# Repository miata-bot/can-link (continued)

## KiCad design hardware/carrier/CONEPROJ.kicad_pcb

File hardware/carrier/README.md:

# Carrier Board

This is the "top" half of the device. It does power management, CAN communication and output control.

## Major Components

| Name | Description |
| ---- | ----------- |
| RP2040 | Main MCU. dual core ARM M0 |
| 3.3v automotive regulator | Power supply for radio, CAN transciever, CAN interface and RP2040 |
| 5.0V automotive regulator | Power supply for the `platform` board |
| RFM69 Packet radio | Packet radio for wireless syncronization |
| Motor driver | 2 motor output motor driver |
| Dual footprint MCP2515 CAN interface | Very popular CAN interface IC. Both packages are placed in the case that one cannot be obtained |
| CAN transciever | driver for CAN communication |
| 2 Buttons | what can i say about buttons |
| 3 status LEDS | control em however u want |
| WS15 LED | first node in a chain of individually addressable LEDS |

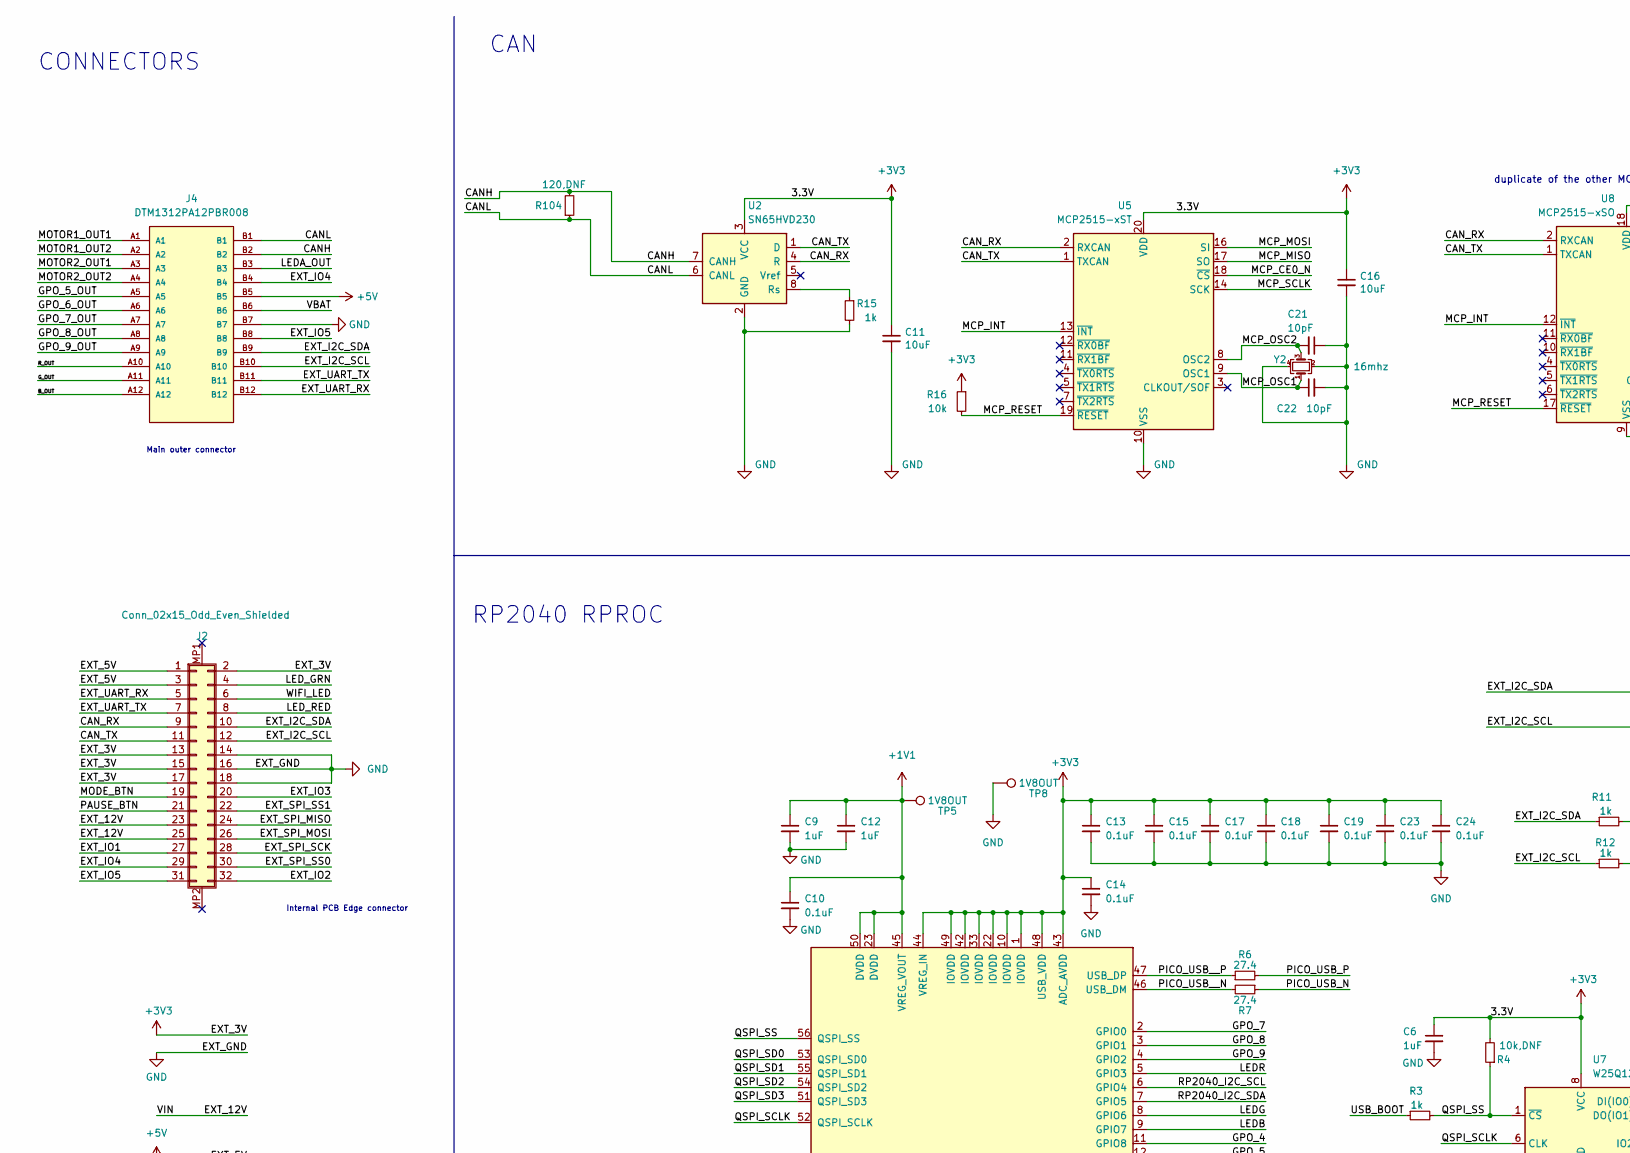
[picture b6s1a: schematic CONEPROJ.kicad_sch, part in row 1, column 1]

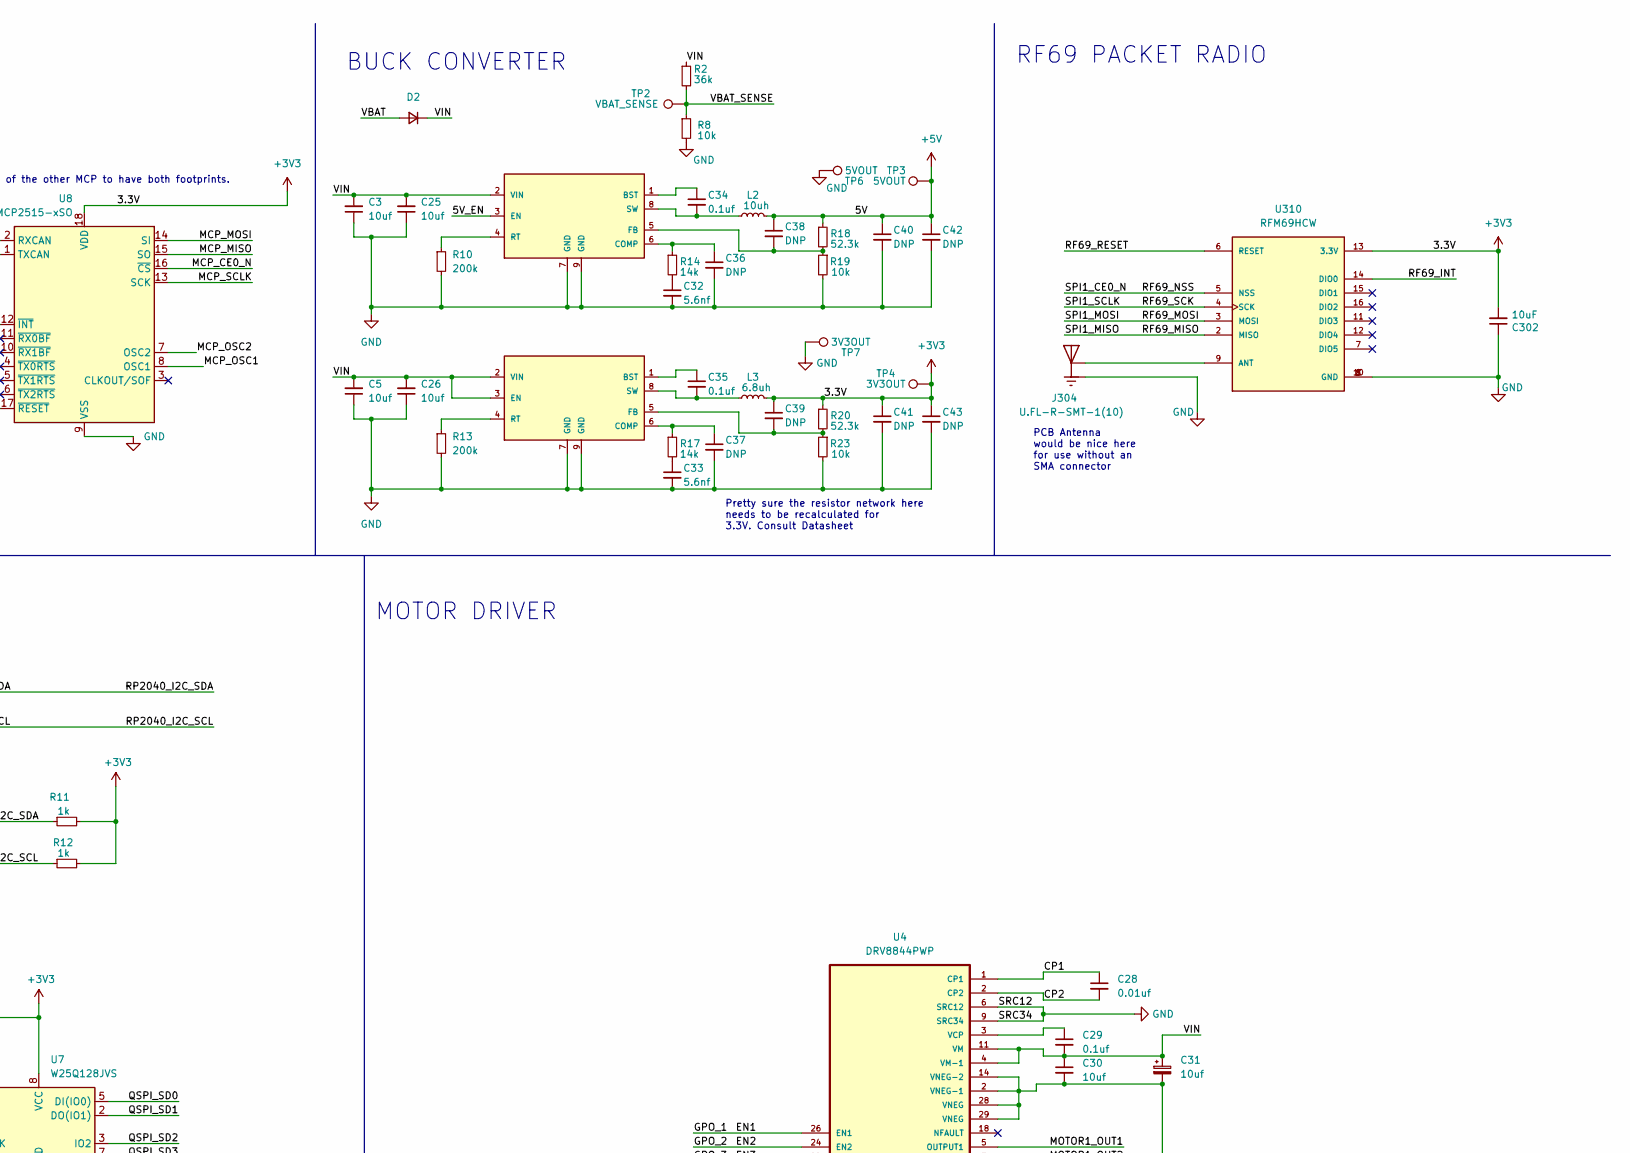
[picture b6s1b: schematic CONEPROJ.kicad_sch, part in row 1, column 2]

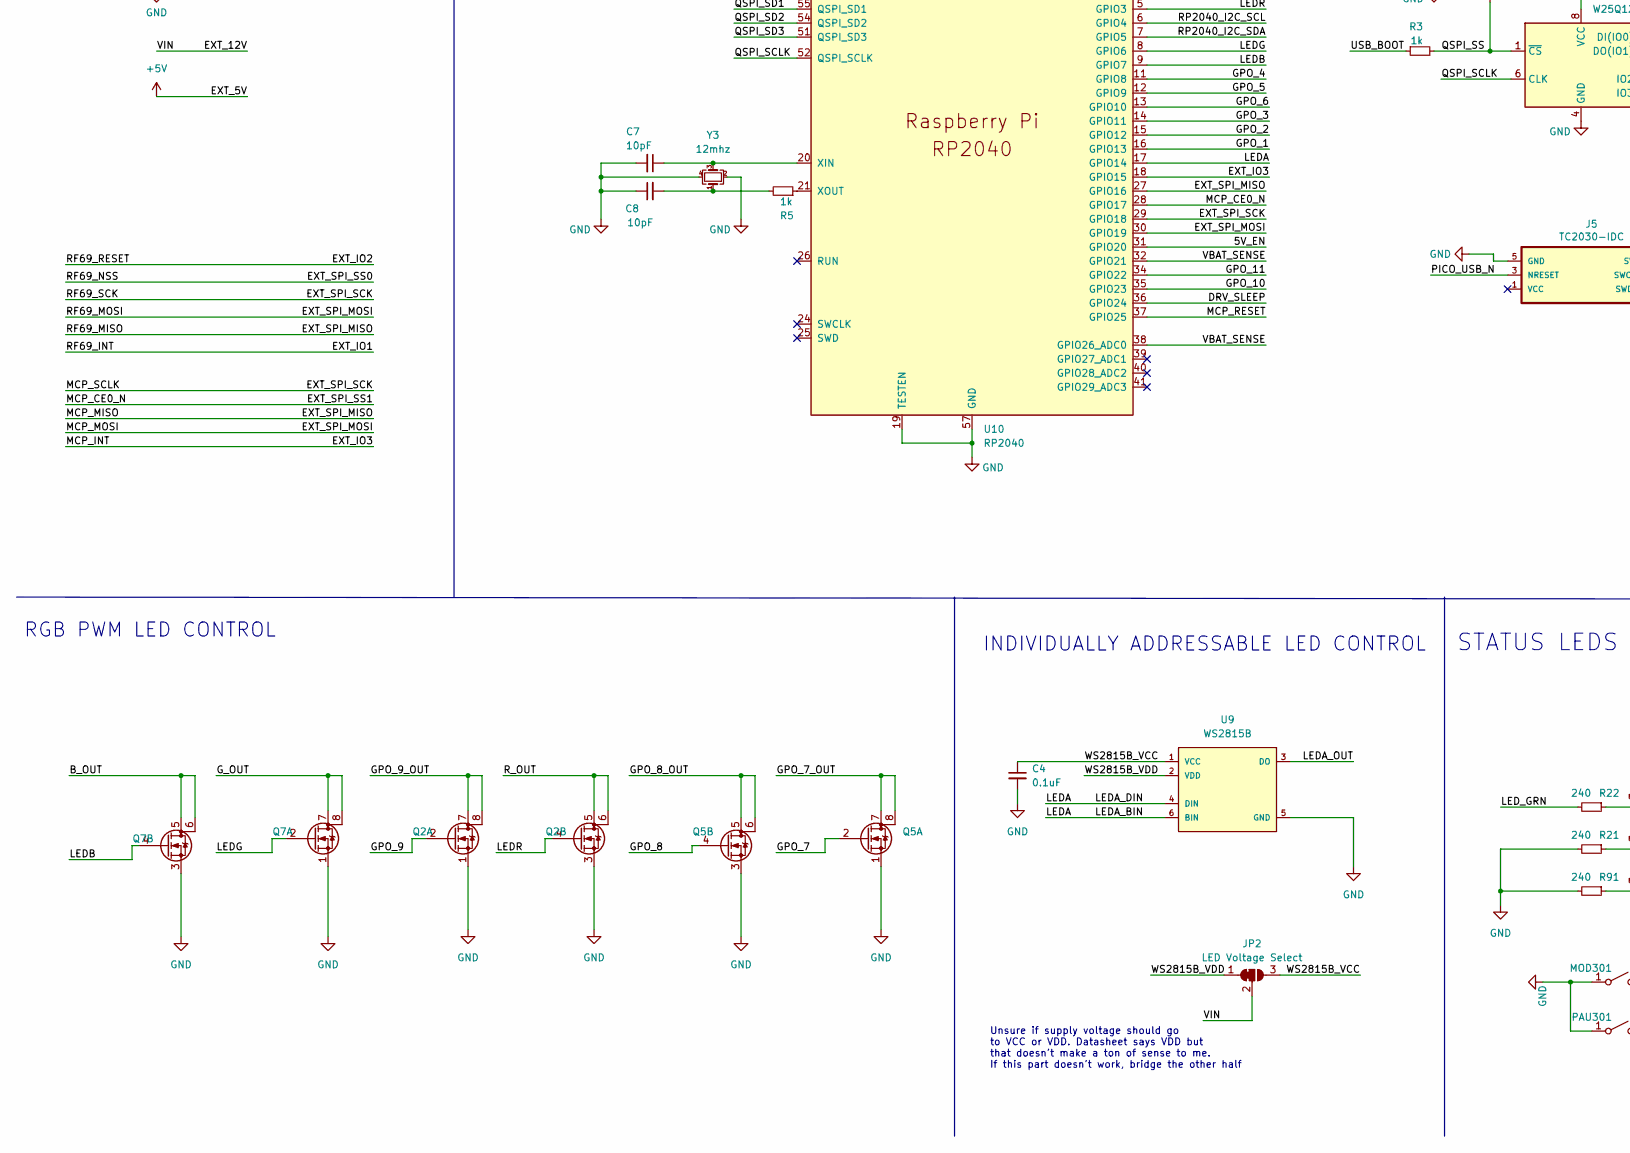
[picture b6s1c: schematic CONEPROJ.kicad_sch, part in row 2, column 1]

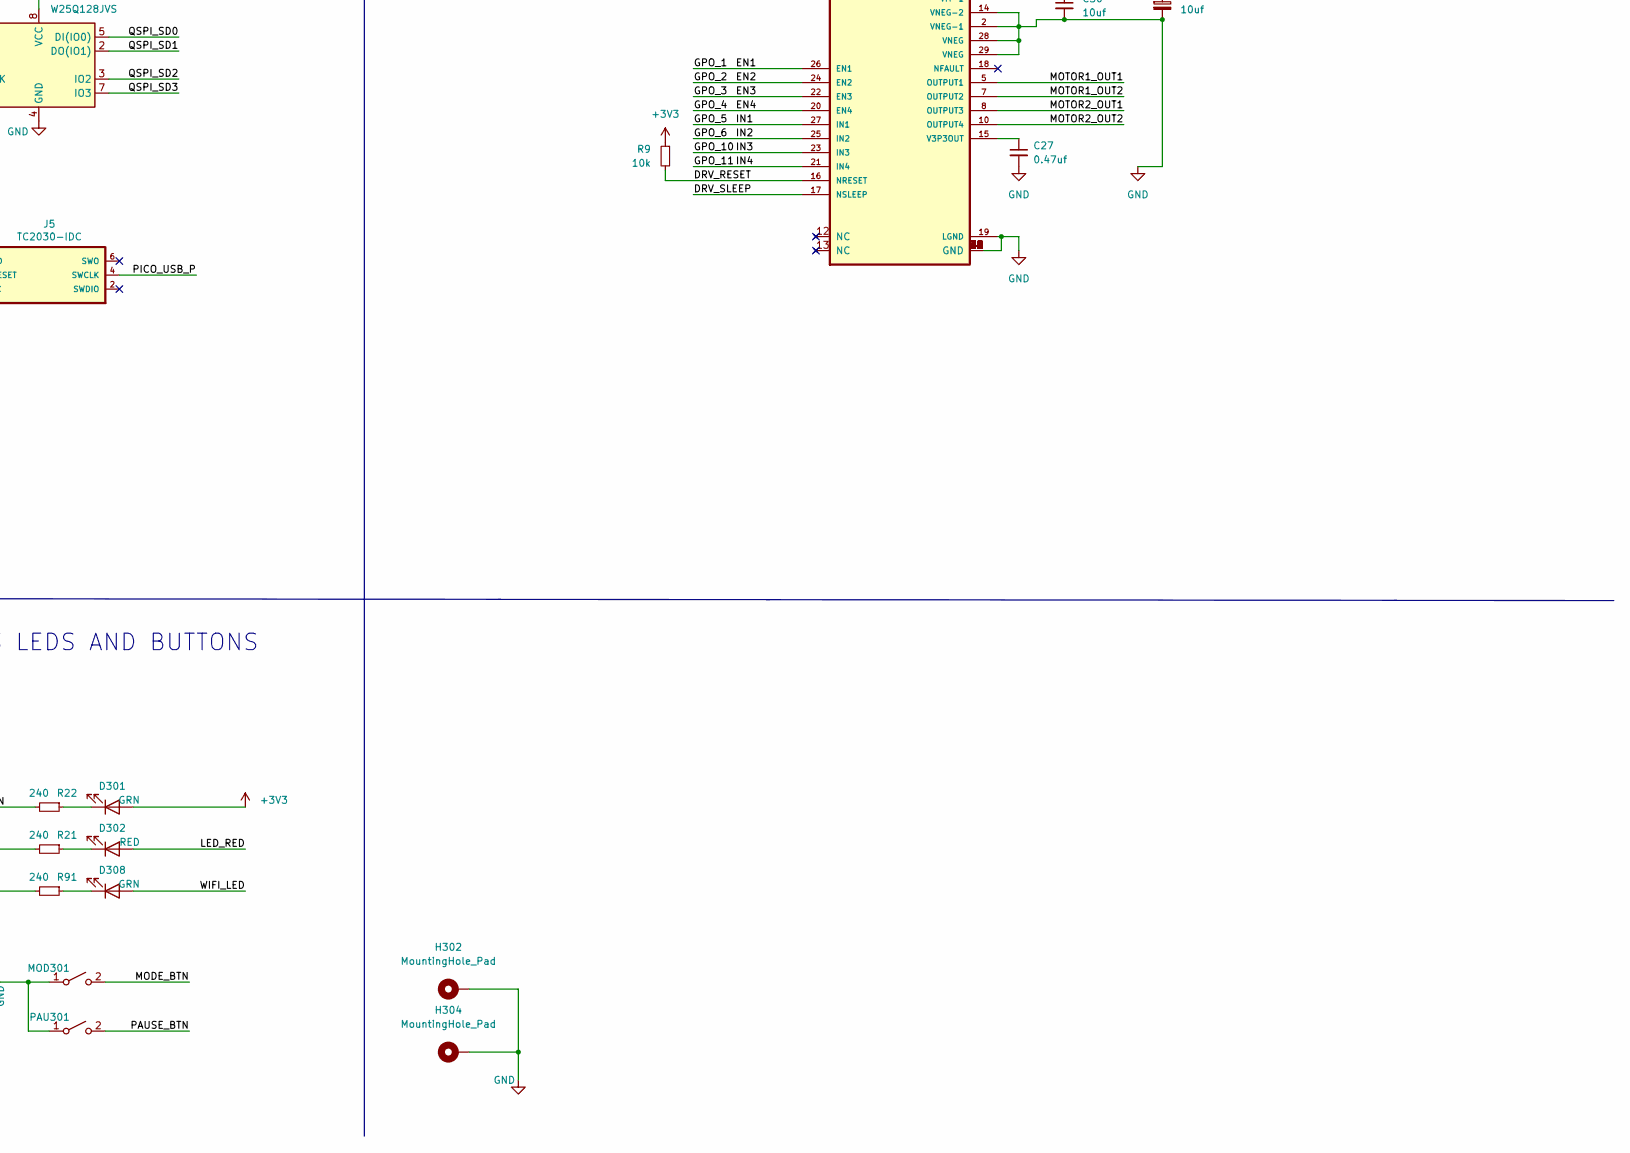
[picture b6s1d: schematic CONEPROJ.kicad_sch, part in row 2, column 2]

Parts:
C3, C5, C25, C26, C30: 10uf; C_0805_2012Metric_Pad1.18x1.45mm_HandSolder; MPN C0805C106M3PAC7800
C4, C10, C13, C14, C15, C17, C18, C19, C23, C24: 0.1uF; C_0603_1608Metric_Pad1.08x0.95mm_HandSolder; MPN C0603C104M5RAC7867
C6, C9, C12: 1uF; C_0603_1608Metric_Pad1.08x0.95mm_HandSolder; MPN CL10B105MO8NNWC
C7, C8, C21, C22: 10pF; C_0603_1608Metric_Pad1.08x0.95mm_HandSolder; MPN C0603C100K5RACAUTO
C11, C16, C302: 10uF; C_0805_2012Metric_Pad1.18x1.45mm_HandSolder; MPN CL21A106KOQNNNE
C27: 0.47uf; C_0805_2012Metric_Pad1.18x1.45mm_HandSolder; MPN CGJ4J2X7R0J474K125AA
C28: 0.01uf; C_0805_2012Metric_Pad1.18x1.45mm_HandSolder; MPN C0805C103K1RAC7210
C29, C34, C35: 0.1uf; C_0805_2012Metric_Pad1.18x1.45mm_HandSolder; MPN 0805 (2012 Metric) 0,94mm
C31: 10uf; CP_Elec_5x5.9; MPN 50TZV10M5X6.1
C32, C33: 5.6nf; C_1206_3216Metric; MPN C1206C562KDRACAUTO
C36, C37, C38, C39, C40, C41, C42, C43: DNP; C_0805_2012Metric_Pad1.18x1.45mm_HandSolder
D2: D_Small; D_SOD-123; MPN PMEG3015EH,115
D301, D308: GRN; LED_0603_1608Metric_Pad1.05x0.95mm_HandSolder; MPN LT Q39E-Q1OO-25-1
D302: RED; LED_0603_1608Metric_Pad1.05x0.95mm_HandSolder; MPN IN-S63ATR
H302, H304: MountingHole_Pad; MountingHole_3.2mm_M3_DIN965_Pad
J2: Conn_02x15_Odd_Even_Shielded; PinSocket_2x16_P1.27mm_Vertical_SMD
J4: DTM1312PA12PBR008; TE_DTM1312PA12PBR008; MPN DTM1312PA12PBR008
J5: TC2030-IDC; Tag-Connect_TC2030-IDC-FP_2x03_P1.27mm_Vertical; MPN2 DNP
J304: U.FL-R-SMT-1(10); HRS_U.FL-R-SMT-1(10); MPN U.FL-R-SMT-1(10)
JP2: LED Voltage Select; SolderJumper-3_P1.3mm_Bridged12_RoundedPad1.0x1.5mm_NumberL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
L2: 10uh; L_Bourns-SRN6028; MPN SRN6028-100M
L3: 6.8uh; L_Bourns-SRN6028; MPN SRN6028-6R8M
MOD301: SW_SPST; SW_RS-032G05A3-SMRT; MPN RS-032G05A3-SM RT
PAU301: SW_SPST; SW_RS-032G05A3-SMRT; MPN RS-032G05A3-SM RT
Q2, Q5, Q7: Q_Dual_NMOS_S1G1S2G2D2D2D1D1; SO-8_3.9x4.9mm_P1.27mm; MPN STS8DNF3LL
R2: 36k; R_0603_1608Metric_Pad0.98x0.95mm_HandSolder; MPN RMCF0603JT36K0
R3, R5, R11, R12, R15: 1k; R_0603_1608Metric_Pad0.98x0.95mm_HandSolder; MPN RMCF0603JT1K00
R4: 10k,DNF; R_0603_1608Metric_Pad0.98x0.95mm_HandSolder; MPN RMCF0603JT10K0
R6, R7: 27.4; C_0603_1608Metric_Pad1.08x0.95mm_HandSolder; MPN RMCF0603FT27R4
R8: 10k; R_0603_1608Metric_Pad0.98x0.95mm_HandSolder; MPN RC0603JR-07240RL
R9, R16, R19, R23: 10k; R_0603_1608Metric_Pad0.98x0.95mm_HandSolder; MPN RMCF0603JT10K0
R10, R13: 200k; R_0603_1608Metric_Pad0.98x0.95mm_HandSolder; MPN RMCF0603JT200K
R14, R17: 14k; R_0603_1608Metric_Pad0.98x0.95mm_HandSolder; MPN RMCF0603FT14K0
R18, R20: 52.3k; R_0603_1608Metric_Pad0.98x0.95mm_HandSolder; MPN RMCF0603FT52K3
R21, R22, R91: 240; R_0603_1608Metric_Pad0.98x0.95mm_HandSolder; MPN RC0603JR-07240RL
R104: 120,DNF; R_0603_1608Metric_Pad0.98x0.95mm_HandSolder; MPN RMCF0603FT120R
TP2: VBAT_SENSE; TestPoint_Pad_D1.0mm
TP3, TP6: 5VOUT; TestPoint_Pad_D1.0mm
TP4, TP7: 3V3OUT; TestPoint_Pad_D1.0mm
TP5, TP8: 1V8OUT; TestPoint_Pad_D1.0mm
U2: SN65HVD230; SOIC-8_3.9x4.9mm_P1.27mm; MPN SN65HVD230D
U3, U6: AP64200Q; SOIC-8-1EP_3.9x4.9mm_P1.27mm_EP2.29x3mm_ThermalVias; MPN AP64200QSP-13
U4: DRV8844PWP; IC_TPS61196PWPRQ1; MPN DRV8844PWP
U5: MCP2515-xST; TSSOP-20_4.4x6.5mm_P0.65mm; MPN MCP2515-I/ST
U7: W25Q128JVS; SOIC-8_5.23x5.23mm_P1.27mm; MPN W25Q128JVS
U8: MCP2515-xSO; SOIC-18W_7.5x11.6mm_P1.27mm; MPN MCP2515-I/SO
U9: WS2815B; worldsemi-WS2815B-MFG; MPN WS2815B
U10: RP2040; RP2040-QFN-56; MPN SC0914(13)
U310: RFM69HCW; XCVR_RFM69HW; MPN COM-13909
Y2: 16mhz; Crystal_SMD_2520-4Pin_2.5x2.0mm; MPN FA-20H 16.0000MF10Z-AJ5
Y3: 12mhz; Crystal_SMD_3225-4Pin_3.2x2.5mm_HandSoldering; MPN NX3225SA-12.000M-STD-CSR-1

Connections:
+1V1: C9.1, C10.1, C12.1, TP5.1, U10.23 (DVDD), U10.45 (VREG_VOUT), U10.50 (DVDD)
+3V3: C6.1, C11.1, C13.1, C14.1, C15.1, C16.1, C17.1, C18.1, C19.1, C23.1, C24.1, C39.1, C41.1, C43.1, C302.2, D301.2 (A), J2.2, J2.13, J2.15, J2.17, L3.2, R4.2, R9.1, R11.2, R12.2, R16.1, R20.1, TP4.1, U2.3 (VCC), U5.20 (VDD), U7.8 (VCC), U8.18 (VDD), U10.1 (IOVDD), U10.10 (IOVDD), U10.22 (IOVDD), U10.33 (IOVDD), U10.42 (IOVDD), U10.43 (ADC_AVDD), U10.44 (VREG_IN), U10.48 (USB_VDD), U10.49 (IOVDD), U310.13 (3.3V)
+5V: C38.1, C40.1, C42.1, J2.1, J2.3, J4.B5, L2.2, R18.1, TP3.1
/5V_EN: U3.3 (EN), U10.31 (GPIO20)
/B_OUT: J4.A12, Q7.5 (D), Q7.6 (D)
/CANH: J4.B2, R104.2, U2.7 (CANH)
/CANL: J4.B1, R104.1, U2.6 (CANL)
/CAN_RX: J2.9, U2.4 (R), U5.2 (RXCAN), U8.2 (RXCAN)
/CAN_TX: J2.11, U2.1 (D), U5.1 (TXCAN), U8.1 (TXCAN)
/CP1: C28.1, U4.1 (CP1)
/DRV_RESET: R9.2, U4.16 (NRESET)
/DRV_SLEEP: U4.17 (NSLEEP), U10.36 (GPIO24)
/EN1: U4.26 (EN1), U10.16 (GPIO13)
/EN2: U4.24 (EN2), U10.15 (GPIO12)
/EN3: U4.22 (EN3), U10.14 (GPIO11)
/EN4: U4.20 (EN4), U10.11 (GPIO8)
/EXT_12V: C3.2, C5.2, C25.2, C26.2, C29.2, C30.1, C31.1, D2.1 (K), J2.23, J2.25, JP2.2 (C), R2.1, U3.2 (VIN), U4.4 (VM-1), U4.11 (VM), U6.2 (VIN), U6.3 (EN)
/EXT_I2C_SCL: J2.12, J4.B10, R12.1, U10.6 (GPIO4)
/EXT_I2C_SDA: J2.10, J4.B9, R11.1, U10.7 (GPIO5)
/EXT_IO1: J2.27, U310.14 (DIO0)
/EXT_IO2: J2.32, U310.6 (RESET)
/EXT_IO3: J2.20, U5.13 (~INT), U8.12 (~INT), U10.18 (GPIO15)
/EXT_IO4: J2.29, J4.B4
/EXT_IO5: J2.31, J4.B8
/EXT_SPI_MISO: J2.24, U5.17 (SO), U8.15 (SO), U10.27 (GPIO16), U310.2 (MISO)
/EXT_SPI_MOSI: J2.26, U5.16 (SI), U8.14 (SI), U10.30 (GPIO19), U310.3 (MOSI)
/EXT_SPI_SCK: J2.28, U5.14 (SCK), U8.13 (SCK), U10.29 (GPIO18), U310.4 (SCK)
/EXT_SPI_SS0: J2.30, U310.5 (NSS)
/EXT_SPI_SS1: J2.22, U5.18 (~CS), U8.16 (~CS), U10.28 (GPIO17)
/EXT_UART_RX: J2.5, J4.B12
/EXT_UART_TX: J2.7, J4.B11
/GPO_5: U4.27 (IN1), U10.12 (GPIO9)
/GPO_5_OUT: J4.A5
/GPO_6: U4.25 (IN2), U10.13 (GPIO10)
/GPO_6_OUT: J4.A6
/GPO_7: Q5.2 (G), U10.2 (GPIO0)
/GPO_7_OUT: J4.A7, Q5.7 (D), Q5.8 (D)
/GPO_8: Q5.4 (G), U10.3 (GPIO1)
/GPO_8_OUT: J4.A8, Q5.5 (D), Q5.6 (D)
/GPO_9: Q2.2 (G), U10.4 (GPIO2)
/GPO_9_OUT: J4.A9, Q2.7 (D), Q2.8 (D)
/GPO_10: U4.23 (IN3), U10.35 (GPIO23)
/GPO_11: U4.21 (IN4), U10.34 (GPIO22)
/G_OUT: J4.A11, Q7.7 (D), Q7.8 (D)
/LEDA: U9.4 (DIN), U9.6 (BIN), U10.17 (GPIO14)
/LEDA_OUT: J4.B3, U9.3 (DO)
/LEDB: Q7.4 (G), U10.9 (GPIO7)
/LEDG: Q7.2 (G), U10.8 (GPIO6)
/LEDR: Q2.4 (G), U10.5 (GPIO3)
/LED_GRN: J2.4, R22.2
/LED_RED: D302.2 (A), J2.8
/MCP_OSC1: C22.1, U5.9 (OSC1), U8.8 (OSC1), Y2.1
/MCP_OSC2: C21.2, U5.8 (OSC2), U8.7 (OSC2), Y2.3
/MCP_RESET: R16.2, U5.19 (~RESET), U8.17 (~RESET), U10.37 (GPIO25)
/MODE_BTN: J2.19, MOD301.2 (B)
/MOTOR1_OUT1: J4.A1, U4.5 (OUTPUT1)
/MOTOR1_OUT2: J4.A2, U4.7 (OUTPUT2)
/MOTOR2_OUT1: J4.A3, U4.8 (OUTPUT3)
/MOTOR2_OUT2: J4.A4, U4.10 (OUTPUT4)
/PAUSE_BTN: J2.21, PAU301.2 (B)
/PICO_USB_N: J5.3 (NRESET), R7.1
/PICO_USB_P: J5.4 (SWCLK), R6.2
/PICO_USB__N: R7.2, U10.46 (USB_DM)
/PICO_USB__P: R6.1, U10.47 (USB_DP)
/QSPI_SCLK: U7.6 (CLK), U10.52 (QSPI_SCLK)
/QSPI_SD0: U7.5 (DI(IO0)), U10.53 (QSPI_SD0)
/QSPI_SD1: U7.2 (DO(IO1)), U10.55 (QSPI_SD1)
/QSPI_SD2: U7.3 (IO2), U10.54 (QSPI_SD2)
/QSPI_SD3: U7.7 (IO3), U10.51 (QSPI_SD3)
/QSPI_SS: R3.2, R4.1, U7.1 (~CS), U10.56 (QSPI_SS)
/R_OUT: J4.A10, Q2.5 (D), Q2.6 (D)
/USB_BOOT: R3.1
/VBAT: D2.2 (A), J4.B6
/VBAT_SENSE: R2.2, R8.1, TP2.1, U10.32 (GPIO21), U10.38 (GPIO26_ADC0)
/WIFI_LED: D308.2 (A), J2.6
/WS2815B_VCC: C4.1, JP2.3 (B), U9.1 (VCC)
/WS2815B_VDD: JP2.1 (A), U9.2 (VDD)
unnamed: C7.1, U10.20 (XIN), Y3.3
unnamed: C8.2, R5.2, Y3.1
unnamed: C27.1, U4.15 (V3P3OUT)
unnamed: C29.1, U4.3 (VCP)
unnamed: C32.1, R14.2
unnamed: C33.1, R17.2
unnamed: C34.1, U3.1 (BST)
unnamed: C34.2, L2.1, U3.8 (SW)
unnamed: C35.1, U6.1 (BST)
unnamed: C35.2, L3.1, U6.8 (SW)
unnamed: C36.1, R14.1, U3.6 (COMP)
unnamed: C37.1, R17.1, U6.6 (COMP)
unnamed: C38.2, R18.2, R19.1, U3.5 (FB)
unnamed: C39.2, R20.2, R23.1, U6.5 (FB)
unnamed: D301.1 (K), R22.1
unnamed: D302.1 (K), R21.1
unnamed: D308.1 (K), R91.1
unnamed: J304.2, U310.9 (ANT)
unnamed: R5.1, U10.21 (XOUT)
unnamed: R10.1, U3.4 (RT)
unnamed: R13.1, U6.4 (RT)
unnamed: R15.1, U2.8 (Rs)

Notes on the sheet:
PCB Antenna would be nice here for use without an SMA connector
duplicate of the other MCP to have both footprints.
RP2040 RPROC
Unsure if supply voltage should go to VCC or VDD. Datasheet says VDD but that doesn't make a ton of sense to me. If this part doesn't work, bridge the other half
CAN
Main outer connector
INDIVIDUALLY ADDRESSABLE LED CONTROL
Pretty sure the resistor network here needs to be recalculated for 3.3V. Consult Datasheet
CONNECTORS
Internal PCB Edge connector
STATUS LEDS AND BUTTONS
BUCK CONVERTER
MOTOR DRIVER
RF69 PACKET RADIO
RGB PWM LED CONTROL

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
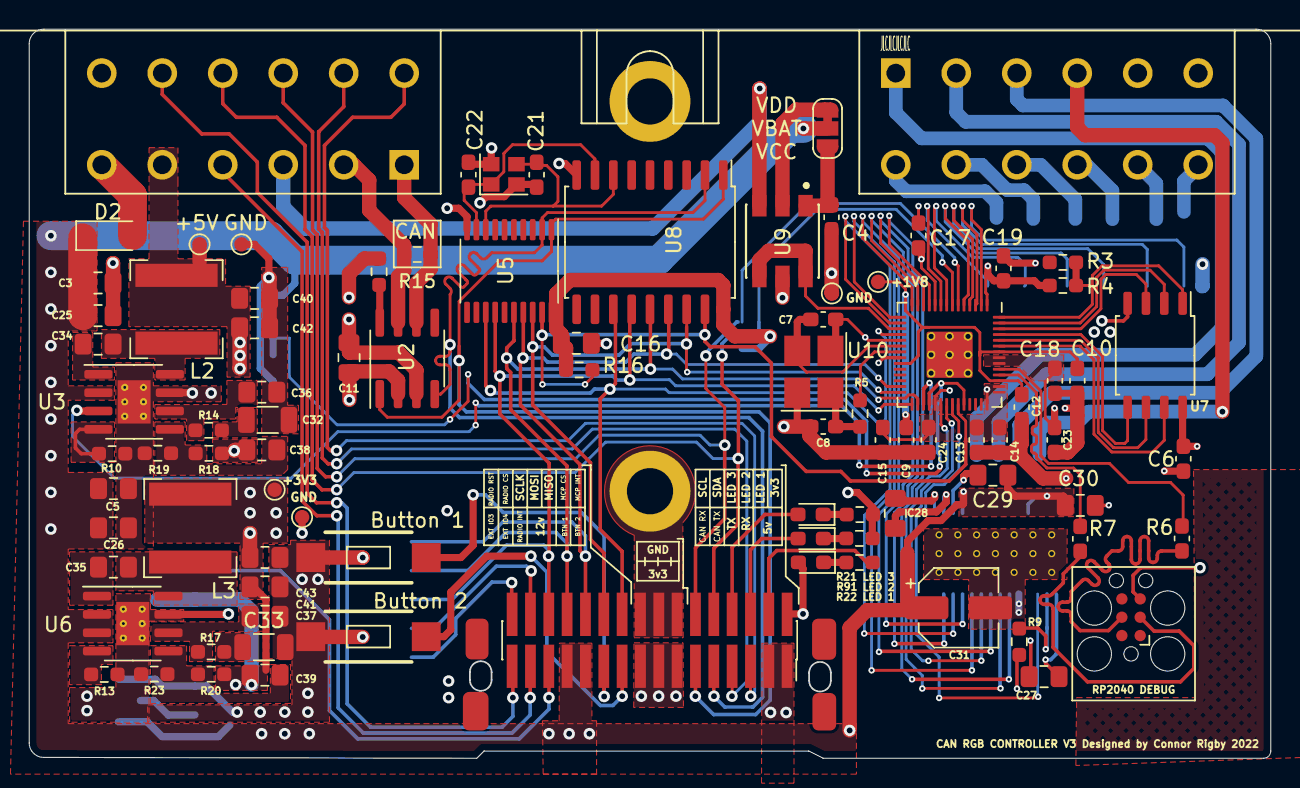
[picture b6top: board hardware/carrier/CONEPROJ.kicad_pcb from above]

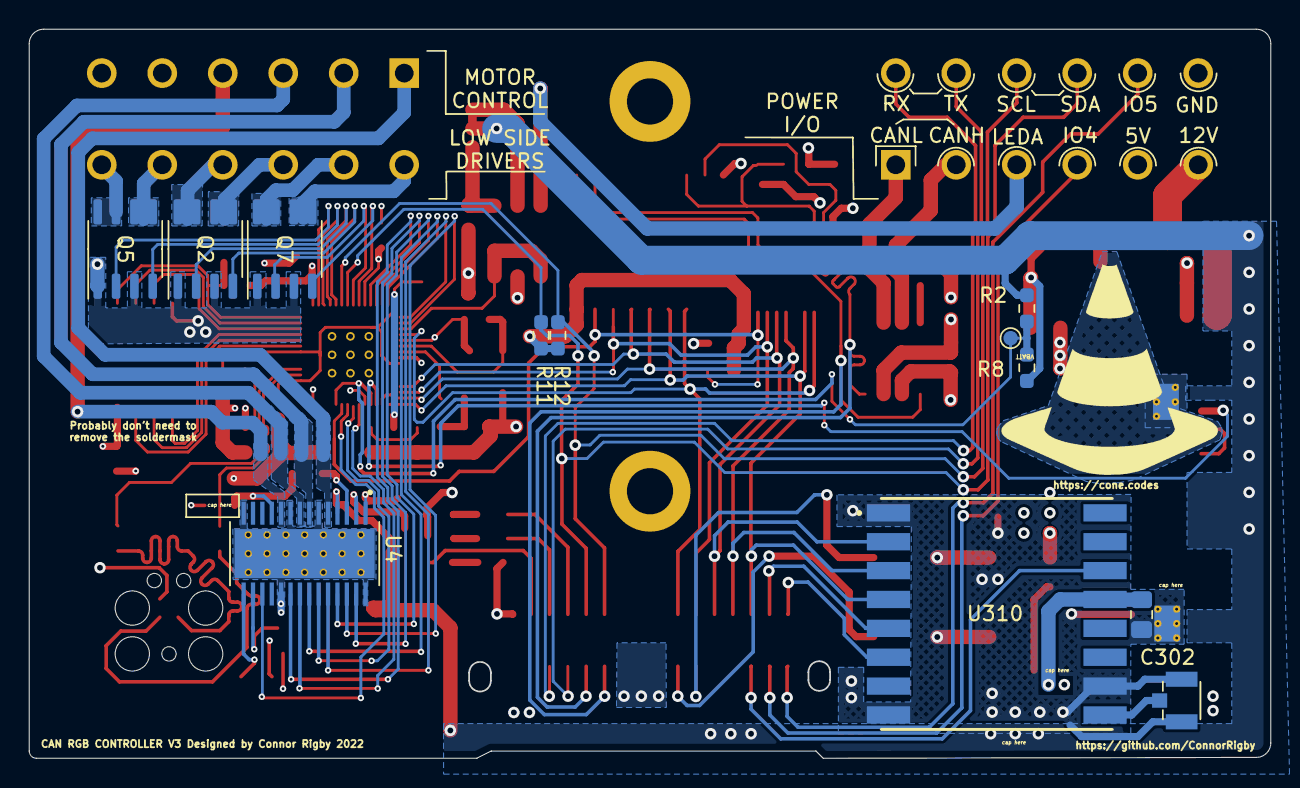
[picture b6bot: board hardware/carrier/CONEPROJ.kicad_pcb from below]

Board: 4 copper layers, 86.0 x 50.5 mm, 102 parts (12 on the bottom side), 98 nets.

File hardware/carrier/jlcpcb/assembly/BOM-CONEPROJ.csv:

Comment,Designator,Footprint,LCSC
0.1uF,"C10,C13,C14,C15,C17,C18,C19,C20,C23,C24,C4",C_0603_1608Metric_Pad1.08x0.95mm_HandSolder,C14663
1uF,"C12,C6,C9",C_0603_1608Metric_Pad1.08x0.95mm_HandSolder,C15849
10uF,"C11,C16,C2,C3,C5",C_0805_2012Metric_Pad1.18x1.45mm_HandSolder,C15850
10pF,"C21,C22,C7,C8",C_0603_1608Metric_Pad1.08x0.95mm_HandSolder,C1634
RP2040,U10,RP2040-QFN-56,C2040
WS2815B,U9,worldsemi-WS2815B-MFG,C965559
W25Q128JVS,U7,SOIC-8_5.23x5.23mm_P1.27mm,C97521
16mhz,Y2,Crystal_SMD_2520-4Pin_2.5x2.0mm,
MCP2515-xSO,U8,SOIC-18W_7.5x11.6mm_P1.27mm,
D_Small,D1,D_SOD-123,
MCP2515-xST,U5,TSSOP-20_4.4x6.5mm_P0.65mm,
27.4,R7,C_0603_1608Metric_Pad1.08x0.95mm_HandSolder,
SW_SPST,PAU301,SW_RS-032G05A3-SMRT,
MountingHole_Pad,H304,MountingHole_3.2mm_M3_DIN965_Pad,
1k,R5,R_0603_1608Metric_Pad0.98x0.95mm_HandSolder,
Conn_02x15_Odd_Even_Shielded,J2,PinSocket_2x16_P1.27mm_Vertical_SMD,
SN65HVD230,U2,SOIC-8_3.9x4.9mm_P1.27mm,
TC2030-IDC,J5,Tag-Connect_TC2030-IDC-FP_2x03_P1.27mm_Vertical,
240,R22,R_0603_1608Metric_Pad0.98x0.95mm_HandSolder,
DTM1312PA12PBR008,J4,TE_DTM1312PA12PBR008,
1k,R15,R_0603_1608Metric_Pad0.98x0.95mm_HandSolder,
SW_SPST,MOD301,SW_RS-032G05A3-SMRT,
1k,R3,R_0603_1608Metric_Pad0.98x0.95mm_HandSolder,
27.4,R6,C_0603_1608Metric_Pad1.08x0.95mm_HandSolder,
RED,D302,LED_0603_1608Metric_Pad1.05x0.95mm_HandSolder,
6.8uH,L1,L_Bourns_SRN6045TA,
"120,DNF",R104,R_0603_1608Metric_Pad0.98x0.95mm_HandSolder,
D_Small,D2,D_SOD-123,
AP1509,U304,SO08,
GRN,D301,LED_0603_1608Metric_Pad1.05x0.95mm_HandSolder,
MountingHole_Pad,H302,MountingHole_3.2mm_M3_DIN965_Pad,
GRN,D308,LED_0603_1608Metric_Pad1.05x0.95mm_HandSolder,
240,R21,R_0603_1608Metric_Pad0.98x0.95mm_HandSolder,
10k,R16,R_0603_1608Metric_Pad0.98x0.95mm_HandSolder,
240,R91,R_0603_1608Metric_Pad0.98x0.95mm_HandSolder,
"10k,DNF",R4,R_0603_1608Metric_Pad0.98x0.95mm_HandSolder,
12mhz,Y3,Crystal_SMD_3225-4Pin_3.2x2.5mm_HandSoldering,
Q_Dual_NMOS_S1G1S2G2D2D2D1D1,Q7,SO-8_3.9x4.9mm_P1.27mm,
Q_Dual_NMOS_S1G1S2G2D2D2D1D1,Q5,SO-8_3.9x4.9mm_P1.27mm,
RFM69HCW,U310,XCVR_RFM69HW,
10uF,C302,C_0805_2012Metric_Pad1.18x1.45mm_HandSolder,
1k,R12,R_0603_1608Metric_Pad0.98x0.95mm_HandSolder,
1k,R11,R_0603_1608Metric_Pad0.98x0.95mm_HandSolder,
Q_Dual_NMOS_S1G1S2G2D2D2D1D1,Q2,SO-8_3.9x4.9mm_P1.27mm,
U.FL-R-SMT-1(10),J304,HRS_U.FL-R-SMT-1(10),
DRV8844PWP,U4,IC_TPS61196PWPRQ1,
6.8uH,L2,L_Bourns_SRN6045TA,
10k,R8,R_0603_1608Metric_Pad0.98x0.95mm_HandSolder,
470nf,C27,C_0805_2012Metric_Pad1.18x1.45mm_HandSolder,
10k,R2,R_0603_1608Metric_Pad0.98x0.95mm_HandSolder,
D_Small,D4,D_SOD-123,
10uF,C25,C_0805_2012Metric_Pad1.18x1.45mm_HandSolder,
10uf,C30,C_0805_2012Metric_Pad1.18x1.45mm_HandSolder,
10uF,C26,C_0805_2012Metric_Pad1.18x1.45mm_HandSolder,
0.1uf,C29,C_0805_2012Metric_Pad1.18x1.45mm_HandSolder,
10uf,C31,CP_Elec_5x5.9,
0.01uf,C28,C_0805_2012Metric_Pad1.18x1.45mm_HandSolder,
AP1509,U3,SO08,
vbat_sense,TP2,TestPoint_Pad_D1.0mm,
